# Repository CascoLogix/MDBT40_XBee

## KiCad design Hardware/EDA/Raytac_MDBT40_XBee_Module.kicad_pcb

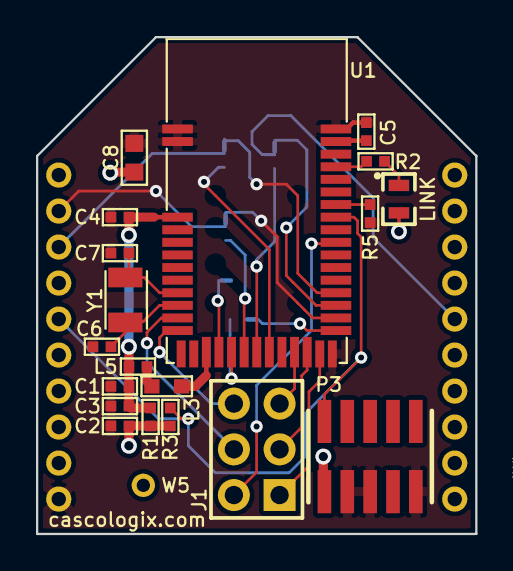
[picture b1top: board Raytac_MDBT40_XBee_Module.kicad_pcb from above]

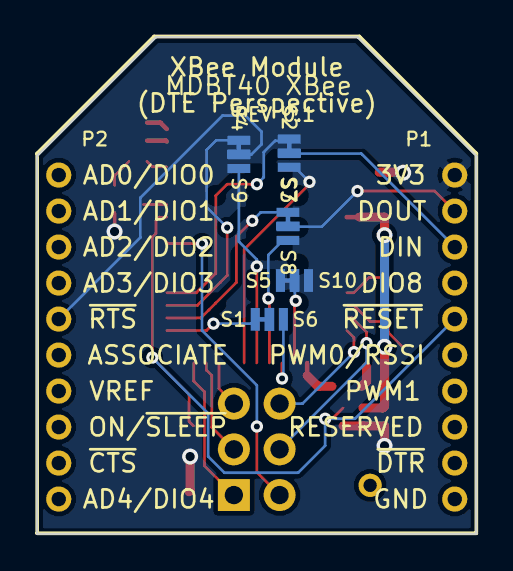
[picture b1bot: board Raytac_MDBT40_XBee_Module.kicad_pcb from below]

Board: 2 copper layers, 24.4 x 27.6 mm, 32 parts (12 on the bottom side), 32 nets.

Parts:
C1, C2: 1uF; C0402
C3: 100pF; C0402
C4: 0.1uF; C0402
C5: 47nF; C0402
C6, C7: 15pF; C0402
C8: 22uF; C0603
DS1: YEL; D0603
J1: TEST POINTS; HEADER_F_100MIL_2R6P_ST_GOLD_PTH
L3: 10uH; L0603
L5: 15nH; L0402
P1: XBEE MODULE PINS; HEADER_XBEE_P1_P10_ALT3
P2: HEADER_M_XBEE_P11-P20_PTH_DTE; HEADER_XBEE_P11_P20_ALT3
P3: JTAG; HEADER_M_1.27MM_2R10P_ST_AU_SMT
R1: 0; R0402
R2: 4.7k; R0402
R3, R5: 12k; R0402
S1, S2, S3, S4, S5: SOLDER_LINK_NC; SOLDER_LINK_50MIL_50MIL_NC
S6, S7, S8, S9, S10: SOLDER_LINK_NO; SOLDER_LINK_50MIL_50MIL_NO
U1: MDBT40
W5: WIRE_PAD_24AWG
Y1: 32.768k; XTAL_3.2MM_1.5MM_SMT

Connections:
/CTS: S4.2, U1.28
/RTS: S1.2, U1.26
/RXD: S2.2, U1.29
/TXD: S3.2, U1.27
CTS_HEADER: P2.16, S4.1, S9.1
GND: C1.2, C2.2, C3.2, C4.1, C5.1, C6.2, C7.2, C8.2, P1.10, P3.3, P3.5, P3.9, R5.2, S5.1, U1.1, U1.2, U1.13, U1.25, U1.42
unnamed: C5.2, U1.41
unnamed: C6.1, U1.10, Y1.2
unnamed: C7.1, U1.9, Y1.1
unnamed: DS1.K, R2.2
unnamed: L3.1, L5.2
unnamed: L3.2, U1.15
unnamed: R2.1, U1.39
unnamed: S6.2, U1.17
unnamed: S7.2, U1.20
unnamed: S8.2, U1.18
unnamed: S9.2, U1.19
unnamed: S5.2, S10.2, U1.16
P0.04: U1.21, W5.1
P0.05: J1.5, U1.22
P0.06: J1.3, U1.23
P0.07: J1.1, U1.24
P0.15: J1.2, U1.33
P0.28: J1.4, U1.11
P0.29: J1.6, U1.12
RTS_HEADER: P2.12, S1.1, S6.1
RXD_HEADER: P1.3, S2.1, S7.1
SWDCLK: P3.4, R5.1, U1.36
SWDIO/RESET: P1.5, P3.2, R3.2, U1.35
TXD_HEADER: P1.2, S3.1, S8.1
VDD: C2.1, C8.1, DS1.A, P1.1, P3.1, R1.1, R3.1, S10.1, U1.14
VDDA: C1.1, C3.1, C4.2, L5.1, R1.2, U1.3

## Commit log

2016-04-09 First commit.
2016-06-14 Swapped CTS and RTS to correct for DTE perspective. Updated schematic.
2016-06-14 Changed board outline to conform to standard Digi XBee outline.
2016-06-14 Updated to remove BLE Nano headers. PCB layout incomplete!
2016-12-12 Updated schematic and board layout. About halfway done routing.
2016-12-17 Moved solder links to make routing easier.
